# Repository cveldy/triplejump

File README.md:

# triplejump

Leverless (Hitbox-style) fighting game controller with ~~three~~ two jump options.

`TODO: One or more images`

## About

This controller is distinguished by its split-hand configuration and angled keyclusters, mitigating the RSI-potential of the standard "hands-together-but-parallel" layout popularized by the Hitbox. The goal is to keep the entire device relatively small while still providing a meaningful ergonomic benefit.

Another notable aspect of the layout is the 10 button right hand cluster. The closeness of the keys in this keyboard-like format makes multi-key inputs (e.g., `LP+LK`) harder than usual to press. Promoting `R3` and `L3` into "first class" buttons mitigates this drawback by providing more locations for macros (the legal kind you can map in-game).

Lastly are the titular ~~three~~ two up buttons. This allows the same handed-preference for jumping (and ability to double-tap using both thumbs) from the normal layout.

Powering this device is OpenStick's excellent [GP2040-CE](https://github.com/OpenStickCommunity/GP2040-CE) gamepad firmware. Please see that repository for information about configuration, console compatibility, and all the rest.

## Creation

If you want to produce one, you will need some parts.

### PCB

- 1x triplejump PCB, created using the [gerbers.zip](./prod/gerbers.zip) files with an online PCB prototyping service. (e.g., [JLCPCB](https://jlcpcb.com/).)
- 1x [RP2040-Zero](https://www.waveshare.com/rp2040-zero.htm).
- 5x 6x6mm Panel PCB Momentary Tactile Mini Push Button Switch DIP 4pin.
- 15x Kailh Choc v1 Hotswap Sockets (PG1350).

### Keys

- 15x Kailh Choc v1 Switches (recommended: linear switches with low actuation force).
- 13x Kailh Choc-compatible 1u Keycaps.
- 2x Kailh Choc-compatible 1.5u Keycaps.

### Case

This case was designed with MBK profile Choc keycaps in mind and may or may not be compatible with other keycaps.

- Laser Cut Acrylic Layers: [Bottom](<./prod/case_layer0_1.5mm.dxf>), [Lower-Middle](<./prod/case_layer1_3mm.dxf>), [Upper-Middle](<./prod/case_layer2_4.5mm.dxf), [Top](<./prod/case_layer3_1.5mm.dxf>)
  - The filenames include how thick each layer should be.
  - The PCB goes between the two middle layers.
- 6x M3 x 12mm Bolts.
- 6x M3 x 6mm Barrel Nuts.
- OPTIONAL: Non-slip Feet or Pads.

### Assembly

- Soldering Equipment.
- Screwdriver.

### Firmware

- The [Latest GP2040-CE Release](https://github.com/OpenStickCommunity/GP2040-CE/releases), flashed accoridng to the documentation.
- Pin (Button) Mapping using GP2040-CE's [Web Configurator](https://gp2040-ce.info/#/web-configurator)
  - There is a catch: the firmware assumes a default pin mapping that the triplejump does not use. Until you've remapped the pins, you must hold down L1 instead of S2 (Start) when plugging in the controller to enter the configurator.
  - You could also short pin 1 to ground manually if you haven't installed the switches yet when setting up the firmware.
  - The correct mapping for the triplejump is shown below.

### Art

Optionally, you could print some art and put it between the top two acrylic layers. An [Art Template](<./prod/triplejump_art_template.psd>) is provided, though I haven't tested it personally.

## Acknowledgments

- [GrooveBob](https://github.com/GroooveBob)'s [Stress](https://github.com/GroooveBob/Stress), which helped inspire this design.
- [jfedor2](https://github.com/jfedor2)'s [Flatbox](https://github.com/jfedor2/flatbox), which helped inspire this design.
- [Afternoon Labs](https://github.com/afternoonlabs)' [Breeze](https://github.com/afternoonlabs/BreezeKeyboard), which helped inspire this design and layout.
- [ruiqimao](https://github.com/ruiqimao)'s [Keyboard PCB Guide](https://github.com/ruiqimao/keyboard-pcb-guide), which led me through the entire PCB creation process.
- [crides](https://github.com/crides)'s [Kleeb](https://github.com/crides/kleeb) Kicad library, whose symbols and footprints are present in the PCB schematic and design.
- [daprice](https://github.com/daprice)'s [keyswitches.pretty](https://github.com/daprice/keyswitches.pretty) Kicad library, whose footprints are present in the PCB design. [CC BY 4.0](https://creativecommons.org/licenses/by/4.0/)
- [Sadek Baroudi](https://github.com/sadekbaroudi)'s [Keyboard Case Design](https://kbd.news/Keyboard-Case-Design-1764.html) article, which showed the process for exporting the PCB into a form usable during case design.
- [OpenStickCommunity](https://github.com/OpenStickCommunity)'s [GP2040-CE](https://github.com/OpenStickCommunity/GP2040-CE), whose firmware makes the silicon useful and whose Discord community was extremely helpful.

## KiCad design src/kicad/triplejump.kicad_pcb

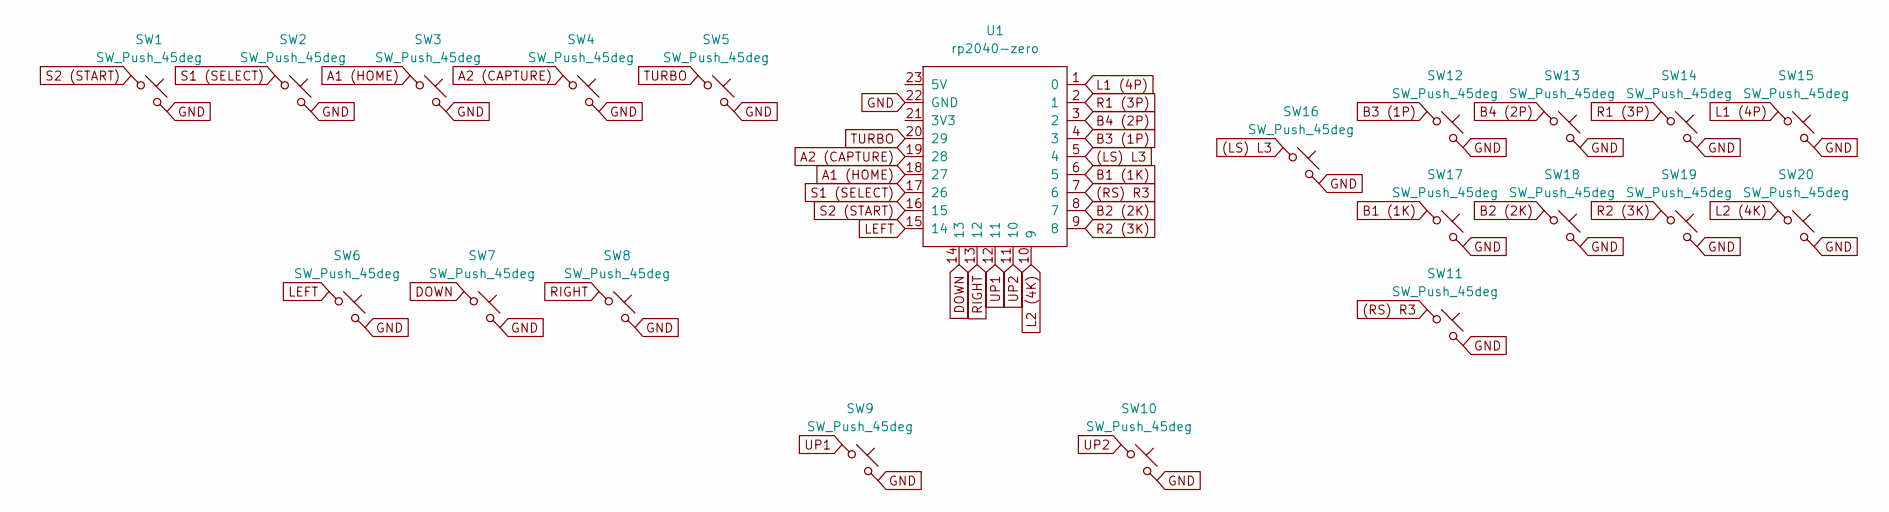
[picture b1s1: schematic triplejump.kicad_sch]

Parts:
SW1, SW2, SW3, SW4: SW_Push_45deg; SW_PUSH_6mm
SW5, SW6, SW7, SW8, SW9, SW10, SW11, SW12, SW13, SW14, SW15, SW16, SW17, SW18, SW19, SW20: SW_Push_45deg; Kailh_socket_PG1350
U1: rp2040-zero; rp2040-zero-tht

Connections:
(LS) L3: SW16.1, U1.5 (4)
(RS) R3: SW11.1, U1.7 (6)
A1 (HOME): SW3.1, U1.18 (27)
A2 (CAPTURE): SW4.1, U1.19 (28)
B1 (1K): SW17.1, U1.6 (5)
B2 (2K): SW18.1, U1.8 (7)
B3 (1P): SW12.1, U1.4 (3)
B4 (2P): SW13.1, U1.3 (2)
DOWN: SW7.1, U1.14 (13)
GND: SW1.2, SW2.2, SW3.2, SW4.2, SW5.2, SW6.2, SW7.2, SW8.2, SW9.2, SW10.2, SW11.2, SW12.2, SW13.2, SW14.2, SW15.2, SW16.2, SW17.2, SW18.2, SW19.2, SW20.2, U1.22 (GND)
L1 (4P): SW15.1, U1.1 (0)
L2 (4K): SW20.1, U1.10 (9)
LEFT: SW6.1, U1.15 (14)
R1 (3P): SW14.1, U1.2 (1)
R2 (3K): SW19.1, U1.9 (8)
RIGHT: SW8.1, U1.13 (12)
S1 (SELECT): SW2.1, U1.17 (26)
S2 (START): SW1.1, U1.16 (15)
TURBO: SW5.1, U1.20 (29)
UP1: SW9.1, U1.12 (11)
UP2: SW10.1, U1.11 (10)

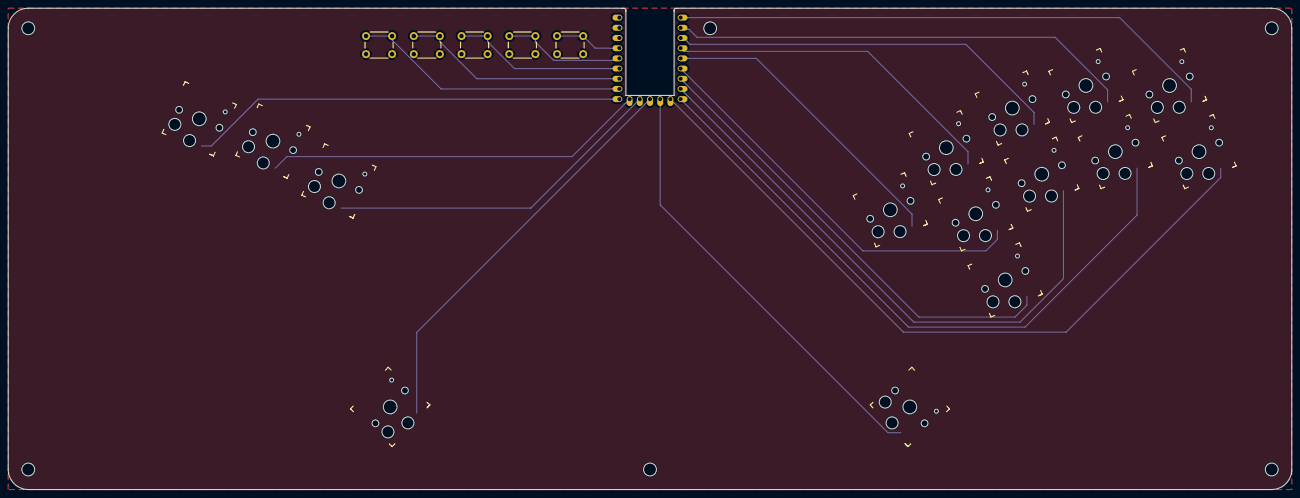
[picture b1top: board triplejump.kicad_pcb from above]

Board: 2 copper layers, 320.0 x 120.0 mm, 27 parts (0 on the bottom side), 21 nets.

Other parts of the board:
M3, M3#2, M3#3, M3#4, M3#5, M3#6: MountingHole_3.2mm_M3

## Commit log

2023-07-01 Catching repo up to current state: kicad done (hopefully)
2023-07-01 Developed README, including many TODOs and NYIs
2023-07-01 Small README update
2023-07-04 Updating README
2023-07-04 Updated PCB (and gerbers) to fix subtle UP 1 missalignment; remove one NPTH
2023-07-04 Creating directories for case creation, starting with DXF->SVG exports of PCB
2023-07-04 First drafts of case design (adding archives to repo, can't seem to move fusion360 working docs w/ free version)
2023-07-04 More small README fixes
2023-07-04 Added stl files for first draft of case, both the raw F360 output and the version auto-fixed with other software
2023-07-04 Attempting to update case links in README.
2023-07-04 More README link fix
2023-07-04 One more README fix: missed file extensions
2023-07-04 Final links fixed in README.
2023-07-11 Removed central m3 screwhole from pcb.
2023-07-19 Redesigned case after failure of first prototype. Now more high profile, has a better USB-C cutout, and is overall much less material.
2023-07-19 Fixed significant issue with v2 of the case.
2023-08-01 Fixed incorrect silkscreen label locations for RT, LB.
2023-08-01 After 2 failed attempts at 3D printing a case, trying out acrylic instead.
2023-08-01 Fixed broken link in README.
2023-09-08 Finalized case and case assembly information.
2024-10-10 Updated PCB for version 2
2024-10-10 Updated README (partially) for v2
2024-10-21 Fixed spacing error in right hand cluster
2024-10-30 Created new case files for v2
2024-10-30 Updated README and pin mapping image.
2024-10-30 Minor update to README acknowledgments.
2024-11-13 Fixed upper case layers and created art template
2024-11-13 Updated README to mention art template and switch from threaded inserts to barrel nuts.
